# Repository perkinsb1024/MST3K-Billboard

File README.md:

# MST3K-Billboard
Code and PCB files to create a Mystery Science Therater 3000 blinking billboard. Build instructions are available at https://bitwise.bperki.com/2018/12/15/building-a-blinking-mystery-science-theater-3000-billboard/

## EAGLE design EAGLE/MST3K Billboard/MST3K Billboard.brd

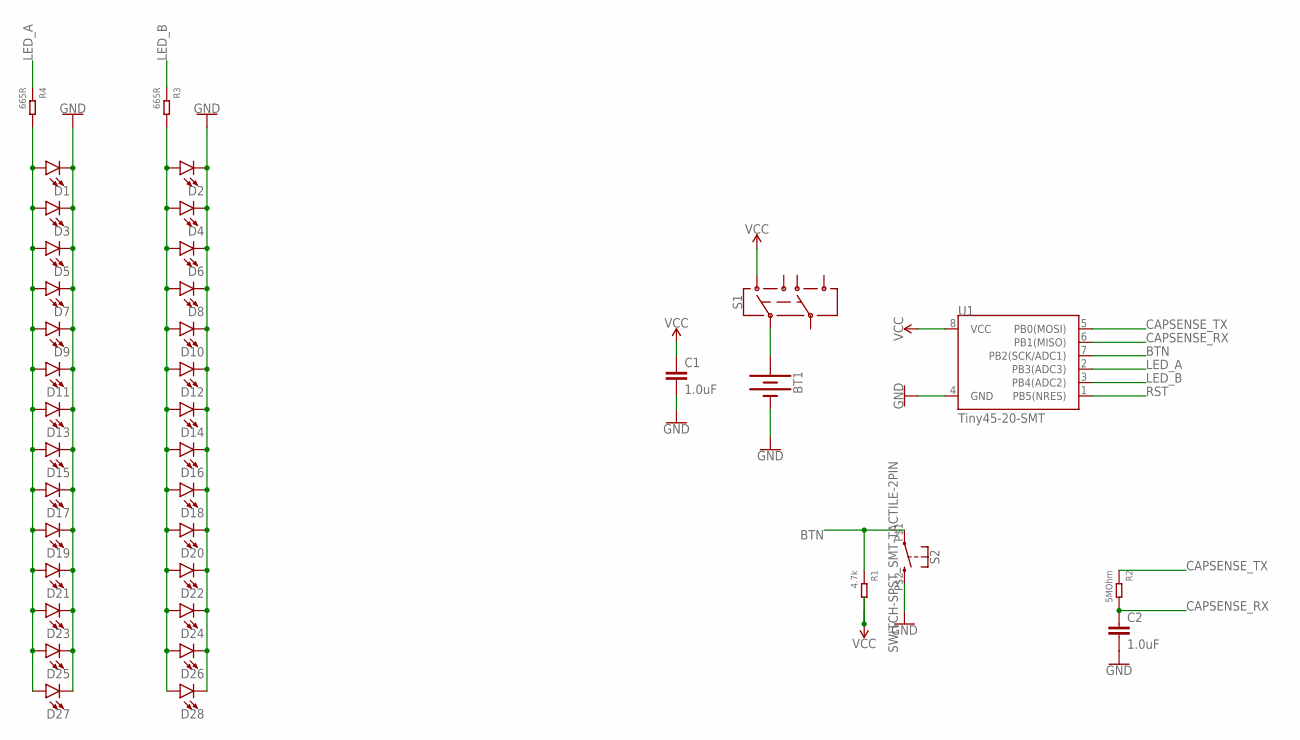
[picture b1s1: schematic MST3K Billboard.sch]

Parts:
BT1: BATTERY-20MM_SMD_4LEGS; BATTCON_20MM_4LEGS
C1, C2: 1.0uF; 0805
D1, D2, D3, D4, D5, D6, D7, D8, D9, D10, D11, D12, D13, D14, D15, D16, D17, D18, D19, D20, D21, D22, D23, D24, D25, D26, D27, D28: LED-3MM-NO_SILK; LED_3MM-NS
R1: 4.7k; R0805
R2: 5MOhm; R0805
R3, R4: 665R; R0805
S1: SWITCH-DPDT-JS202011JCQN; SWITCH_DPDT_SMD_JS202011JCQN
S2: SWITCH-SPST_SMT-TACTILE-2PIN; SMT_TACTILE_SWITCH_3X2MM
U1: Tiny45-20-SMT; SO08-EIAJ_MCU

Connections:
BTN: R1.1, S2.P$1 (1), U1.7 (PB2(SCK/ADC1))
CAPSENSE_RX: C2.1, R2.2, U1.6 (PB1(MISO))
CAPSENSE_TX: R2.1, U1.5 (PB0(MOSI))
GND: BT1.NEGATIVE (-), C1.2, C2.2, D1.K (C), D2.K (C), D3.K (C), D4.K (C), D5.K (C), D6.K (C), D7.K (C), D8.K (C), D9.K (C), D10.K (C), D11.K (C), D12.K (C), D13.K (C), D14.K (C), D15.K (C), D16.K (C), D17.K (C), D18.K (C), D19.K (C), D20.K (C), D21.K (C), D22.K (C), D23.K (C), D24.K (C), D25.K (C), D26.K (C), D27.K (C), D28.K (C), S2.P$2 (2), U1.4 (GND)
LED_A: R4.1, U1.2 (PB3(ADC3))
LED_B: R3.1, U1.3 (PB4(ADC2))
unnamed: BT1.POSITIVE@1 (+), BT1.POSITIVE@2 (+), BT1.POSITIVE@3 (+), BT1.POSITIVE@4 (+), S1.P$2 (2)
OUT1: D1.A, D3.A, D5.A, D7.A, D9.A, D11.A, D13.A, D15.A, D17.A, D19.A, D21.A, D23.A, D25.A, D27.A, R4.2
OUT2: D2.A, D4.A, D6.A, D8.A, D10.A, D12.A, D14.A, D16.A, D18.A, D20.A, D22.A, D24.A, D26.A, D28.A, R3.2
RST: U1.1 (PB5(NRES))
VCC: C1.1, R1.2, S1.P$1 (1), U1.8 (VCC)

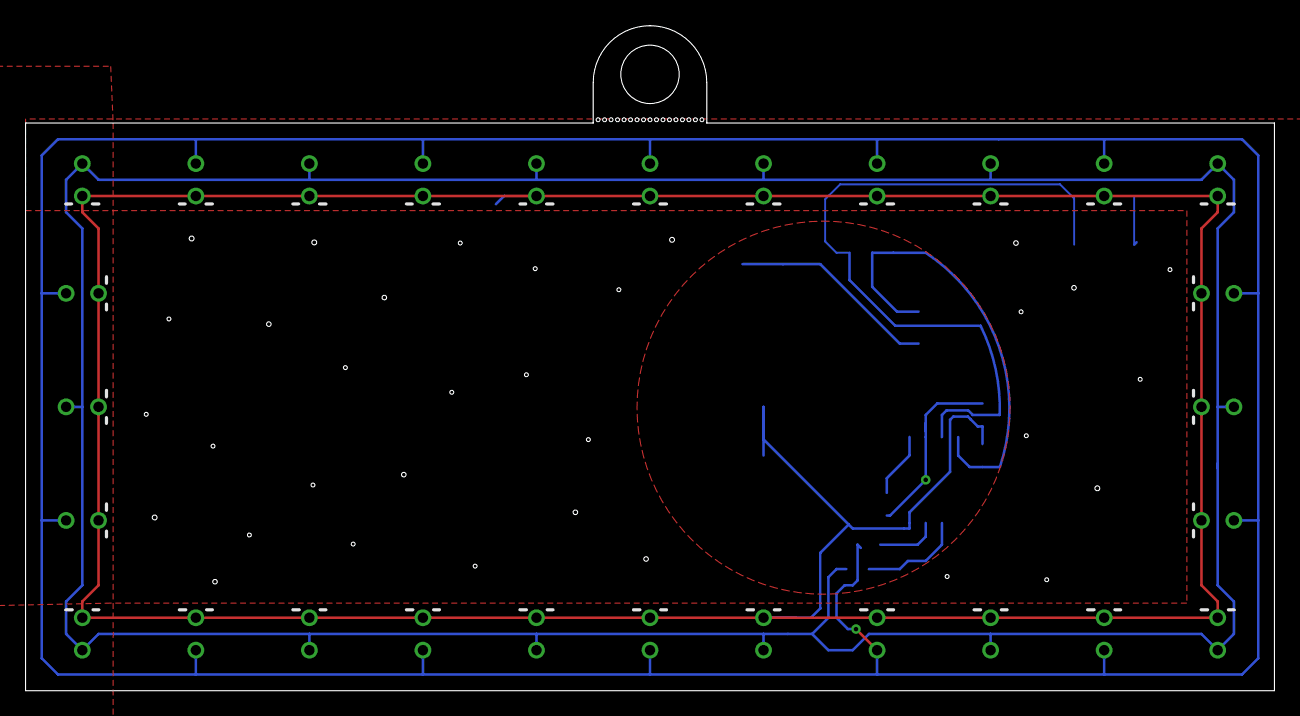
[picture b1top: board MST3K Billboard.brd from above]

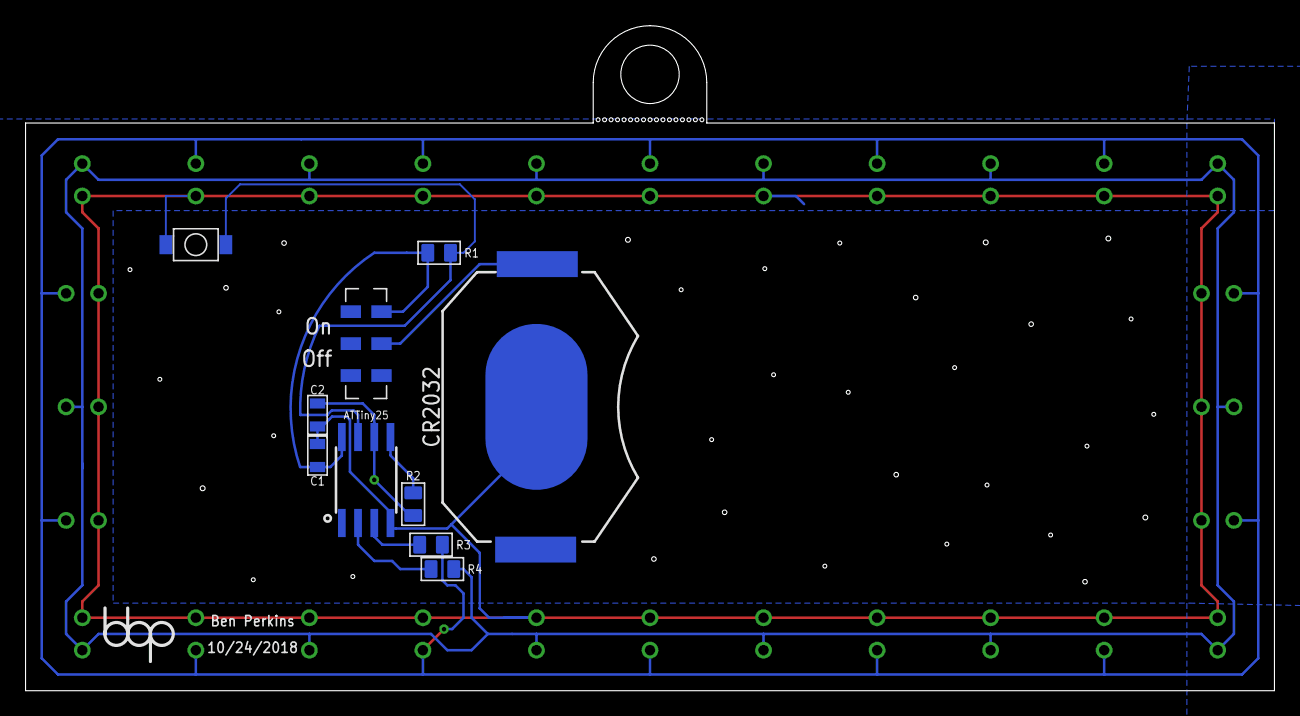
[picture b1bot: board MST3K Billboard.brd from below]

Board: 2 copper layers, 97.8 x 52.1 mm, 38 parts (10 on the bottom side), 10 nets.

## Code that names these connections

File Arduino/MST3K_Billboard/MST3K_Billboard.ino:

#include <avr/sleep.h>
#include <avr/interrupt.h>
#include <EEPROM.h>

#define LED_A_PIN 3
#define LED_B_PIN 4
#define BUTTON_PIN 2

#define LONG_PRESS_DURATION_MS 1000
#define DEBOUNCE_DELAY_MS 100
#define BTN_NO_PRESS 0
#define BTN_SHORT_PRESS 1
#define BTN_LONG_PRESS 2

#define FIRST_BLINK_DURATION_MS 4000
#define BLINK_DURATION_MS 2500
#define DELAY_XLONG 30000
#define DELAY_LONG 10000
#define DELAY_SHORT 5000

#define EEPROM_BRIGHTNESS_ADDR 0
#define EEPROM_SAVE_DELAY_MS 5000

#define BRIGHTNESS_STEPS 32
#define FULL_BRIGHTNESS (BRIGHTNESS_STEPS)
#define HALF_BRIGHTNESS (BRIGHTNESS_STEPS >> 1)
#define QUARTER_BRIGHTNESS (BRIGHTNESS_STEPS >> 2)
#define EIGHTH_BRIGHTNESS (BRIGHTNESS_STEPS >> 3)
#define MIN_BRIGHTNESS 1
#define OFF 0

uint8_t globalBrightness = EEPROM.read(EEPROM_BRIGHTNESS_ADDR);
bool globalButtonReady = true;

ISR(PCINT0_vect) {
  // Define the ISR so that the ATTiny doesn't reset when it's triggered, but it doesn't need to do anything
}

void sleep() {
  // From https://bigdanzblog.wordpress.com/2014/08/10/attiny85-wake-from-sleep-on-pin-state-change-code-example/
  GIMSK |= _BV(PCIE);                     // Enable Pin Change Interrupts
  PCMSK |= _BV(PCINT2);                   // Use PB2 as interrupt pin
  set_sleep_mode(SLEEP_MODE_PWR_DOWN);    // Go to power down mode when sleeping
  sleep_enable();                         // Sets the Sleep Enable bit in the MCUCR Register (SE BIT)
  sei();                                  // Enable interrupts
  sleep_cpu();                            // Sleep
  // Code execution will resume here when an interrupt is triggered
  cli();                                  // Disable interrupts
  PCMSK &= ~_BV(PCINT2);                  // Turn off PB3 as interrupt pin
  sleep_disable();                        // Clear SE bit
  sei();                                  // Enable interrupts so timing functions work
}

inline bool buttonPressed() {
  return !digitalRead(BUTTON_PIN);
}

uint8_t getButtonPress() {
  uint32_t firstPressTime = millis();
  if (buttonPressed()) {
    // Don't accept another button press until this one ends
    if (!globalButtonReady) {
      return BTN_NO_PRESS;
    }
    globalButtonReady = false;
    delay(DEBOUNCE_DELAY_MS);
    while (buttonPressed()) {
      if (millis() - firstPressTime > LONG_PRESS_DURATION_MS) {
        return BTN_LONG_PRESS;
      }
    }
    return BTN_SHORT_PRESS;
  }
  // If we got here, the button isn't pressed, so we're ready to read another
  globalButtonReady = true;
  return BTN_NO_PRESS;
}

void setLeds(uint8_t brightnessA, uint8_t brightnessB, uint16_t cycles) {
  do {
    for (uint8_t i = 0; i < BRIGHTNESS_STEPS; i++) {
      digitalWrite(LED_A_PIN, i < brightnessA);
      digitalWrite(LED_B_PIN, i < brightnessB);
    }
  }
  while (cycles--);
}

uint8_t blinkEffect(uint8_t brightness, uint16_t durationMs) {
  uint32_t endTime = millis() + durationMs;
  uint8_t buttonPressMode = BTN_NO_PRESS;
  while (millis() < endTime) {
    setLeds(brightness, OFF, 6);
    setLeds(OFF, OFF, 6);
    setLeds(OFF, brightness, 6);
    setLeds(OFF, OFF, 6);
    
    // Check the button to end early
    buttonPressMode = getButtonPress();
    if (buttonPressMode != BTN_NO_PRESS) {
      return buttonPressMode;
    }
  }
  return buttonPressMode;
}

void pokeMode() {
  uint8_t buttonPressType = BTN_NO_PRESS;
  // Don't allow a brightness of 'OFF' in this mode
  if (globalBrightness == OFF) {
    globalBrightness = MIN_BRIGHTNESS;
  }
  while (1) {
    // Put the CPU to sleep until an interrupt (button press) wakes it up
    sleep();
    buttonPressType = getButtonPress();
    // Using a while loop because the button may be pressed again during the blink effect
    //  which will restart the effect
    while (buttonPressType == BTN_SHORT_PRESS) {
      buttonPressType = blinkEffect(globalBrightness, BLINK_DURATION_MS);
    }
    if (buttonPressType == BTN_LONG_PRESS) {
      // We're about to leave this mode, so give the user a brief indication
      setLeds(FULL_BRIGHTNESS, FULL_BRIGHTNESS, 1);
      setLeds(OFF, OFF, 100);
      return;
    }
  }
}

void manualMode() {
  bool incrementBrightness = false;
  bool saveNewBrightness = false;
  uint32_t brightnessChangeMs = millis();
  uint8_t buttonPressType = BTN_NO_PRESS;
  while (1) {
    // Check if we need to change the brightness due to a button press
    if (incrementBrightness) {
      switch (globalBrightness) {
        case FULL_BRIGHTNESS:
          globalBrightness = MIN_BRIGHTNESS;
          break;
        case MIN_BRIGHTNESS:
          globalBrightness = QUARTER_BRIGHTNESS;
          break;
        case QUARTER_BRIGHTNESS:
          globalBrightness = HALF_BRIGHTNESS;
          break;
        case HALF_BRIGHTNESS:
        default:
          globalBrightness = FULL_BRIGHTNESS;
          break;
      }
      incrementBrightness = false;
      saveNewBrightness = true;
      brightnessChangeMs = millis();
    }
    buttonPressType = blinkEffect(globalBrightness, BLINK_DURATION_MS);
    if(saveNewBrightness && millis() > brightnessChangeMs + EEPROM_SAVE_DELAY_MS) {
      // Write the brightness value to EEPROM if it has changed and it's been more than 5 seconds
      // This means that if the user is cycling through brightness levels, we only write the last one to EEPROM
      saveNewBrightness = false;
      // It probably doesn't matter, but EEPROM can be read more than it can be written, so don't bother writing if it's the same value
      if(EEPROM.read(EEPROM_BRIGHTNESS_ADDR) != globalBrightness) {
        EEPROM.write(EEPROM_BRIGHTNESS_ADDR, globalBrightness);
      }
    }

    if (buttonPressType == BTN_SHORT_PRESS) {
      incrementBrightness = true;
    }
    else if (buttonPressType == BTN_LONG_PRESS) {
      // We're about to leave this mode, so give the user a brief indication
      setLeds(FULL_BRIGHTNESS, FULL_BRIGHTNESS, 1);
      setLeds(OFF, OFF, 20);
      if(saveNewBrightness) {
        // If the brightness has changed, save the new value regardless of how long ago it happened, since we're about to return
        saveNewBrightness = false;
        if(EEPROM.read(EEPROM_BRIGHTNESS_ADDR) != globalBrightness) {
          EEPROM.write(EEPROM_BRIGHTNESS_ADDR, globalBrightness);
        }
      }
      return;
    }
  }
}

void setup() {
  // Power saving functions.
  ACSR |= _BV(ACD); // Disable ADC.
  ADCSRA &= ~_BV(ADEN); // Disable ADC.
  // Unlock watchdog to allow changes (see datasheet section 8.5.2).
  WDTCR |= (_BV(WDCE) | _BV(WDE));
  // Disable watchdog.
  WDTCR &= ~_BV(WDE);
  WDTCR &= ~_BV(WDIE);

  // Pin setup
  pinMode(BUTTON_PIN, INPUT);
  pinMode(LED_A_PIN, OUTPUT);
  pinMode(LED_B_PIN, OUTPUT);

  // Fade in and out on power-up (helps to ensure the programmer is attached)
  for(uint8_t fade = 0; fade <= FULL_BRIGHTNESS; fade++) {
    setLeds(fade, fade, 5);
  }
  for(uint8_t fade = 0; fade <= FULL_BRIGHTNESS; fade++) {
    setLeds(FULL_BRIGHTNESS-fade, FULL_BRIGHTNESS-fade, 5);
  }
}

void loop() {
  // Start with "poke mode" - LEDs blink for a bit when the button is pressed
  pokeMode();
  // Next mode is "manual" - Button press controls brightness, but LEDs are always blinking
  manualMode();
}

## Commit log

2018-12-16 Added PCB files, Arduino code and 3D print STL files
2018-12-16 Removed unecessary files, added .gitignore

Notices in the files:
parts and their libraries:
SparkFun-LED: Licensing: Creative Commons ShareAlike 4.0 International - https://creativecommons.org/licenses/by-sa/4.0
